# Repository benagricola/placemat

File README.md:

# placemat

Lay out a KiCad board from a Python script, and see what each change did.

A script imports `board`, measures the generated board, declares where
things go and which copper joins them, and `placemat run` does the rest:
generate the board with the `pcb` toolchain, resolve the declarations in
priority order against an offline occupancy model, write through pcbnew,
run DRC, render, and record the run with an impact summary against the
previous one.

```sh
uv venv --python "$(which python3)" --system-site-packages   # pcbnew comes with KiCad, not PyPI
uv sync --extra dev
uv run placemat run boards/x/X_layout.py --label first
uv run pytest
```

`fixtures/` holds real modules with the libraries that build them.
`uv run python fixtures/bench.py` places each of them from scratch under each
configuration and compares the result with the committed `fixtures/bench.json`:
more parts placed, then fewer findings, then shorter wire. A change that can
move a placement runs it first, puts its tally lines in the commit message, and
commits the rewritten baseline (`--update`) with it.

The skill in `skills/placemat` is how an agent works with it; the script
surface is in `skills/placemat/references/api.md`. `PLAN.md` is the plan
this tree was built to.

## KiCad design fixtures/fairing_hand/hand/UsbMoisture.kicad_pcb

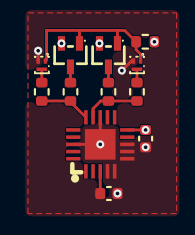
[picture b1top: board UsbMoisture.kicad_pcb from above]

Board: 6 copper layers, 12 parts (0 on the bottom side), 10 nets.

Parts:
C1, C2: CL05B104KB54PNC; C_0402_1005Metric
R1, R2: ERJ-2RKF1004X; R_0402_1005Metric
R3, R4, R5: ERJ-2RKF1003X; R_0402_1005Metric
U1: TPD6S300RUKR; WQFN-20_L3.0-W3.0-P0.40-BL-EP1.7
U2, U3: CSD15380F3; PICOSTAR-3_L0.7-W0.6-P0.35-TL
U4, U5: DMG1013T-7; SC-75-3_L1.6-W0.8-P1.00-LS1.6-BR

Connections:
DOWN1: R1.2, U2.3
DOWN2: R2.2, U3.3
EXCITE: R3.2, U2.1, U3.1, U4.1, U5.1
GND: C1.2, C2.2, U1.4, U1.5, U1.6, U1.7, U1.8, U1.13, U1.18, U1.21, U2.2, U3.2
LD1: R1.1, R4.2, U1.15
LD2: R2.1, R5.2, U1.14
PD_LDO_3V3: C2.1, R3.1, U1.10, U4.2, U5.2
PULL1: R4.1, U4.3
PULL2: R5.1, U5.3
SBU_BIAS: C1.1, U1.3

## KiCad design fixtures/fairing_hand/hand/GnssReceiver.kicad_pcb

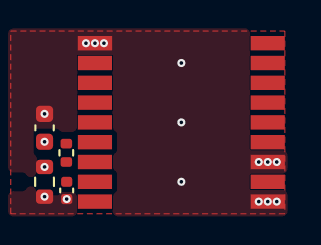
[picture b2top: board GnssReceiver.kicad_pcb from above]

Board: 6 copper layers, 5 parts (0 on the bottom side), 3 nets, no tracks yet.

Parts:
C1: CL10A106MA8NRNC; C_0603_1608Metric
C2: CL05B104KB54PNC; C_0402_1005Metric
FB1: BLM18EG601SZ1D; R_0603_1608Metric
R1: ERJ-2GE0R00X; R_0402_1005Metric
U1: MAX-M10S-00B; GNSS_LCC18_shared_land

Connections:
GND: C1.2, C2.2, U1.1, U1.10, U1.12
GNSS_VCC: C1.1, C2.1, FB1.2, R1.1, U1.6, U1.8
GNSS_VIO: R1.2, U1.7

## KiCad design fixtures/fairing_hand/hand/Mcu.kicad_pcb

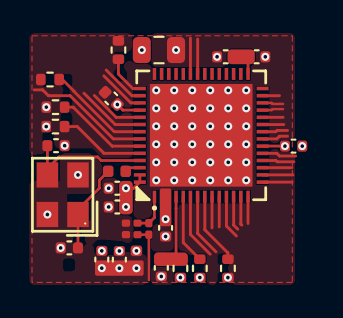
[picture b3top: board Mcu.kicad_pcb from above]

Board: 6 copper layers, 27 parts (0 on the bottom side), 16 nets.

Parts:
C1, C6, C8, C9, C13: CL05B104KB54PNC; C_0402_1005Metric
C2, C7, C10, C12: CL05A105KA5NQNC; C_0402_1005Metric
C3: GRM21BR61H106KE43L; C_0805_2012Metric
C4, C5: GRM0335C1H1R5CA01D; C_0201_0603Metric
C11: CL05B103KB5NNNC; C_0402_1005Metric
C14, C15: GCM1555C1H160FA16D; C_0402_1005Metric
L1: LQP03TN2N4B02D; L_0201_0603Metric
L2: LQG15HN2N0C02D; L_0402_1005Metric
L3: MLG1005S24NJT000; L_0402_1005Metric
R1, R2, R4, R5, R6: 0402WGF1002TCE; R_0402_1005Metric
R3: ERJ-2RKF1000X; R_0402_1005Metric
R7: 0402WGF5100TCE; R_0402_1005Metric
U1: ESP32-S3FH4R2; QFN-56_L7.0-W7.0-P0.40-BL-EP5.7
U2: S3240000101040; CRYSTAL-SMD_4P-L3_2-W2_5-BL

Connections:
BOOT_STRAP: R1.2, U1.5
GND: C1.2, C2.2, C3.2, C4.2, C5.2, C6.2, C7.2, C8.2, C9.2, C10.2, C11.2, C12.2, C13.2, C14.2, C15.2, R5.2, R6.2, U1.57, U2.2, U2.4
LED_STATUS_DRIVE: R3.1, U1.43
MCU_EN: C2.1, R2.2, U1.4
RF_50: C4.1, L1.2
RF_CHIP: C5.1, L1.1, U1.1
STRAP_DOWNLOAD: R6.1, U1.52
STRAP_JTAG: R4.2, U1.8
STRAP_VSPI: R5.1, U1.51
UART_TX_CHIP: R7.1, U1.49
V3V3: C1.1, C3.1, C7.1, C8.1, C9.1, C10.1, C11.1, L2.1, R1.1, R2.1, R4.1, U1.20, U1.46, U1.55, U1.56
VDD_RF: C6.1, L2.2, U1.2, U1.3
VDD_SPI: C12.1, C13.1, U1.29
XTAL_1: C14.1, L3.2, U2.1
XTAL_N: C15.1, U1.53, U2.3
XTAL_P: L3.1, U1.54

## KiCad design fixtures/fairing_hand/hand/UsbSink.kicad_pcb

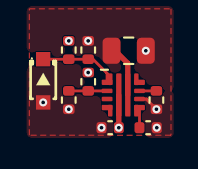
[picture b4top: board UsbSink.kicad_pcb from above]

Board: 6 copper layers, 10 parts (0 on the bottom side), 7 nets.

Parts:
C1: CL05B104KB54PNC; C_0402_1005Metric
C2: CL21A225KBQNNNE; C_0805_2012Metric
C3: CL05B103KB5NNNC; C_0402_1005Metric
D1: MM3Z5V1ST1G; SOD-323_L1.7-W1.3-LS2.5-RD
R1, R4: ERJ-2RKF1003X; R_0402_1005Metric
R2: 0402WGF2203TCE; R_0402_1005Metric
R3: ERJ-2RKF6651X; R_0402_1005Metric
R5: 0402WGF4023TCE; R_0402_1005Metric
U1: TPS259470LRPWR; RPW0010A

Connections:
GND: C1.2, C2.2, C3.2, D1.2, R1.2, R3.2, R4.2, U1.8
SINK_EN: D1.1, R1.1, R2.2, U1.1
SINK_LIMIT: R3.1, U1.9
SINK_OVLO: R4.1, R5.2, U1.2
SINK_SLEW: C3.1, U1.7
VBUS: C1.1, R2.1, R5.1, U1.5
VSHUNT: C2.1, U1.6

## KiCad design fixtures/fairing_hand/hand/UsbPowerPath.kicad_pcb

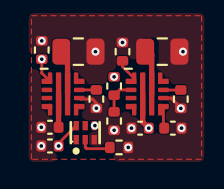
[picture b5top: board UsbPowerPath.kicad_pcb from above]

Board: 6 copper layers, 16 parts (0 on the bottom side), 13 nets.

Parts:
C1, C2, C5: GCM155R71H104KE02D; C_0402_1005Metric
C3, C6: UMK212BB7225KG-T; C_0805_2012Metric
C4: GCM155R71H103KA55D; C_0402_1005Metric
R1, R3, R5, R7: ERJ-2RKF1003X; R_0402_1005Metric
R2: ERJ-2RKF6651X; R_0402_1005Metric
R4: 400k; R_0402_1005Metric
R6: ERJ-2RKF9760X; R_0402_1005Metric
U1, U3: TPS259470LRPWR; RPW0010A
U2: SN74LVC1G08DRYR; SON-6_L1.5-W1.0-P0.50-BL

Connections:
GND: C1.2, C2.2, C3.2, C4.2, C5.2, C6.2, R1.2, R2.2, R3.2, R5.2, R6.2, R7.2, U1.8, U2.3, U3.8
PC_IN: C2.1, R4.1, U1.5
PD_SINK: R1.1, U1.1
PD_SOURCE: R7.1, U2.2
SINK_LIMIT: R2.1, U1.9
SINK_OVLO: R3.1, R4.2, U1.2
SINK_SLEW: C4.1, U1.7
SOURCE_EN: R5.1, U2.4, U3.1
SOURCE_LIMIT: R6.1, U3.9
USB_HV: C5.1, U3.5
V3V3: C1.1, U2.6
VBUS: C6.1, U3.6
VSHUNT: C3.1, U1.6

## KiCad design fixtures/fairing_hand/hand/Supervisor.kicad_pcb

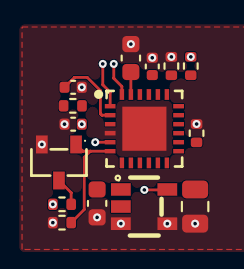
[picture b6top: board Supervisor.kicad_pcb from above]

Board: 6 copper layers, 15 parts (0 on the bottom side), 10 nets.

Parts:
C1: CL10A105KB8NNNC; C_0603_1608Metric
C2: GRM21BR61H106KE43L; C_0805_2012Metric
C3: CL05B103KB5NNNC; C_0402_1005Metric
C4, C5: CL05B104KB54PNC; C_0402_1005Metric
C6: CL10B474KA8NNNC; C_0603_1608Metric
R1, R5: ERJ-2RKF1003X; R_0402_1005Metric
R2, R3, R6: ERJ-2RKF1004X; R_0402_1005Metric
R4: ERJ-2RKF4702X; R_0402_1005Metric
U1: TPS7B6933DBVR; TSOT-23-5_L2.9-W1.6-P0.95-LS2.8-BR
U2: MSPM0L1106TRGER; VQFN-24_L4.0-W4.0-P0.50-TL-EP2.5
U3: 2N7002; SOT-23-3_L2.9-W1.3-P1.90-LS2.4-BR

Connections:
GND: C1.2, C2.2, C3.2, C4.2, C5.2, C6.2, R1.2, R2.2, R5.2, U1.3, U1.4, U2.4, U2.25, U3.2
REV_EN: R3.2, U3.3
REV_EN_GATE: R2.1, U2.6, U3.1
SUP_BSL: R1.1, U2.14
SUP_NRST: C3.1, R4.2, U2.2
SUP_VCORE: C6.1, U2.23
VBIKE: R3.1, R6.1
VIN_SENSE: C4.1, R5.1, R6.2, U2.21
VPROT_IN: C1.1, U1.1
V_AON: C2.1, C5.1, R4.1, U1.5, U2.3

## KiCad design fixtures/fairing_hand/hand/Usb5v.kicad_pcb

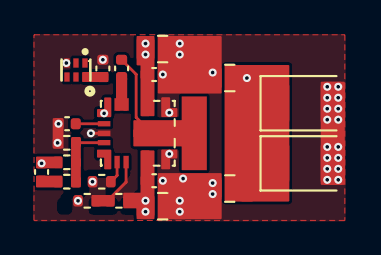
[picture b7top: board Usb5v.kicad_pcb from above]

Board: 6 copper layers, 21 parts (0 on the bottom side), 11 nets.

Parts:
C1, C2, C4, C5: CL05B104KB54PNC; C_0402_1005Metric
C3: GCM1555C1H220FA16D; C_0402_1005Metric
C6, C7: CL21A475KBQNNNE; C_0805_2012Metric
C8, C9: GRM21BZ71A226ME15L; C_0805_2012Metric
C10: CL05A105KA5NQNC; C_0402_1005Metric
L1: APH404012C1R5MP01; APH404012_APV_land
R1: ERJ-2RKF2212X; R_0402_1005Metric
R2: ERJ-2RKF1003X; R_0402_1005Metric
R3: RT0402BRD0716K9L; R_0402_1005Metric
R4: RT0402BRD0769K8L; R_0402_1005Metric
R5: ERJ-2RKF1001X; R_0402_1005Metric
R6: ERJ-2RKF5761X; R_0402_1005Metric
U1: LM61440AASQRJRRQ1; VQFN-14_L4.0-W3.5-P0.5-BL-RJR0014A
U2, U3: T520T107M006APE070; CP_EIA-3528-12_Kemet-T
U4: SN74LVC1G07DRYR(UMW); SON-6_L1.5-W1.0-P0.50-BL

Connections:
BST_5V: C1.1, U1.13, U1.14
EN_5V: R1.1, R2.2, U1.7, U4.4
FB_5V: R3.1, R4.2, R5.2, U1.4
FF_5V: C3.2, R5.1
GND: C2.2, C4.2, C5.2, C6.2, C7.2, C8.2, C9.2, C10.2, R1.2, R3.2, R6.2, U1.3, U1.9, U1.11, U2.2, U3.2, U4.3
PP5V: C3.1, C8.1, C9.1, L1.2, R4.1, U1.1, U2.1, U3.1
RT_5V: R6.1, U1.6
SW_5V: C1.2, L1.1, U1.10
V3V3: C2.1, U4.6
VCC_5V: C10.1, U1.2
VSHUNT: C4.1, C5.1, C6.1, C7.1, R2.1, U1.8, U1.12

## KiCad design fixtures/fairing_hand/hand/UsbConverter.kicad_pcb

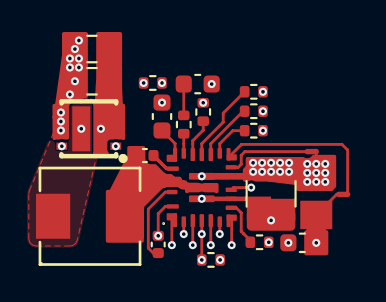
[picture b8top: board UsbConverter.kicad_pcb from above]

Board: 6 copper layers, 22 parts (0 on the bottom side), 22 nets.

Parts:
C1, C2: CL05B104KB54PNC; C_0402_1005Metric
C3: 0603B222K500NT; C_0603_1608Metric
C4, C5: GRM21BR61H106KE43L; C_0805_2012Metric
C6: GMK325BJ226MM-T; C_1210_3225Metric
C7: GRM188C81E475ME11D; C_0603_1608Metric
C8: CL10A106MA8NRNC; C_0603_1608Metric
NT1, NT2: NetTie-2_SMD_Pad0.3mm
R1, R7: ERJ-2GE0R00X; R_0402_1005Metric
R2, R3, R8: ERJ-2RKF1003X; R_0402_1005Metric
R4, R5: 0402WGF1002TCE; R_0402_1005Metric
R6: ERJ-2RKF5102X; R_0402_1005Metric
R9: PE1206DRM470R01L; PE1206_Yageo_Table8
U1: MWSA0518S-2R2MT; IND-SMD_L5.4-W5.2
U2: AON7934; DFN-8_L3.0-W3.0-P0.65-BL_AON7934
U3: TPS55288RPMR; RPM0026A

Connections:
AGND: C3.2, C8.2, R1.1, R3.2, R5.2, R6.2, R7.2, U3.7, U3.10
BB_FAULT: R2.2, U3.14
BOOT1: C1.1, U3.22
BOOT2: C2.1, U3.20
CDC_SET: R3.1, U3.16
COMP_BB: R4.1, U3.18
COMP_MID: C3.1, R4.2
DR1H: U2.1, U3.2
DR1L: U2.8, U3.1
FSW_SET: R5.1, U3.8
GND: C4.2, C5.2, C6.2, C7.2, R1.2, R8.2, U2.5, U2.6, U2.7, U3.9, U3.24
ILIM_BB: R6.1, U3.17
ISN: NT1.2, U3.13
ISP: NT2.2, U3.12
MODE_BB: R7.1, U3.15
SW1: C1.2, U1.1, U2.10, U3.23
SW2: C2.2, U1.2, U3.21, U3.25
VBUS: C7.1, NT1.1, R9.2
VBUS_EN: R8.1, U3.4
VCC_BB: C8.1, U3.19
VOUT: C6.1, NT2.1, R9.1, U3.11, U3.26
VSHUNT: C4.1, C5.1, U2.2, U2.3, U2.4, U2.9, U3.3
